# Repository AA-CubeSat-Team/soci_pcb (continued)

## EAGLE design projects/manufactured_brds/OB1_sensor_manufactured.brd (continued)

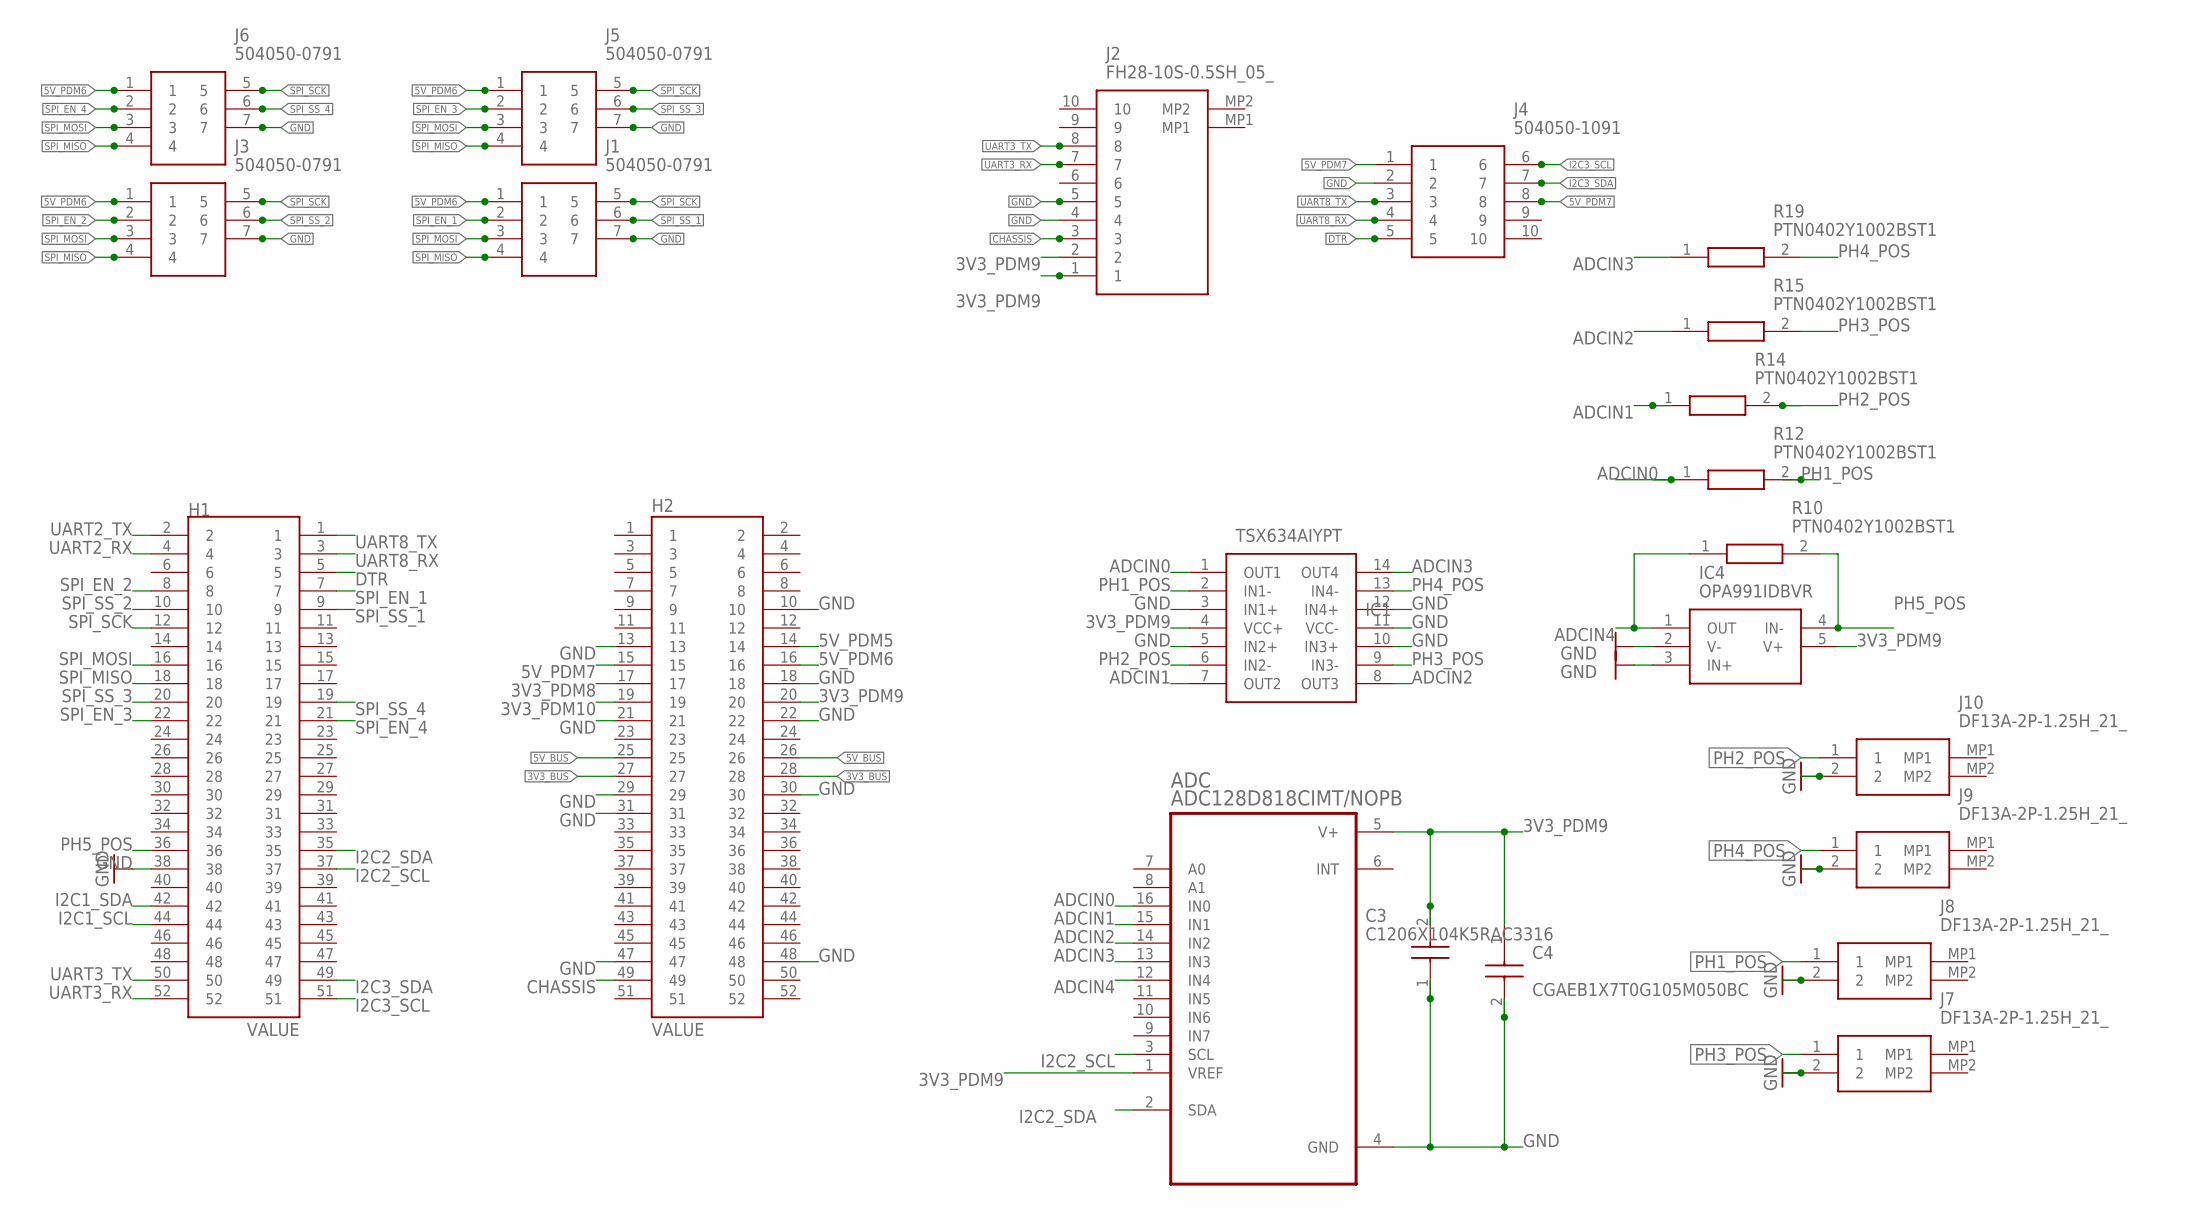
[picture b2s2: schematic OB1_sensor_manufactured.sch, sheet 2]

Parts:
ADC: ADC128D818CIMT/NOPB; SOP65P640X120-16N
C3: C1206X104K5RAC3316; CAPC3316X98N
C4: CGAEB1X7T0G105M050BC; CAPC0611X68N
H1, H2: ESQ-126-39-G-D; SAMTEC_ESQ-126-39-G-D
IC1: TSX634AIYPT; SOP65P640X120-14N
IC4: OPA991IDBVR; SOT95P280X145-5N
J1, J3, J5, J6: 504050-0791
J2: FH28-10S-0.5SH_05_; FH2810S05SH05
J4: 504050-1091
J7, J8, J9, J10: DF13A-2P-1.25H_21_; DF13A2P125H21
R10, R12, R14, R15, R19: PTN0402Y1002BST1; RESC1106X84N

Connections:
3V3_BUS: H2.27, H2.28
3V3_PDM8: H2.17
3V3_PDM9: ADC.1 (VREF), ADC.5 (V+), C3.2, C4.1, H2.20, IC1.4 (VCC+), IC4.5 (V+), J2.1, J2.2; also elsewhere on the board
3V3_PDM10: H2.19
5V_BUS: H2.25, H2.26; also elsewhere on the board
5V_PDM5: H2.14
5V_PDM6: H2.16, J1.1, J3.1, J5.1, J6.1
5V_PDM7: H2.15, J4.1, J4.8
ADCIN0: ADC.16 (IN0), IC1.1 (OUT1), R12.1
ADCIN1: ADC.15 (IN1), IC1.7 (OUT2), R14.1
ADCIN2: ADC.14 (IN2), IC1.8 (OUT3), R15.1
ADCIN3: ADC.13 (IN3), IC1.14 (OUT4), R19.1
ADCIN4: ADC.12 (IN4), IC4.1 (OUT), R10.1
CHASSIS: H2.49, J2.3
DTR: H1.5, J4.5
GND: ADC.4 (GND), C3.1, C4.2, H1.38, H2.10, H2.13, H2.18, H2.21, H2.22, H2.29, H2.30, H2.31, H2.47, H2.48, IC1.3 (IN1+), IC1.5 (IN2+), IC1.10 (IN3+), IC1.11 (VCC-), IC1.12 (IN4+), IC4.2 (V-), IC4.3 (IN+), J1.7, J2.4, J2.5, J3.7, J4.2, J5.7, J6.7, J7.2, J8.2, J9.2, J10.2; also elsewhere on the board
I2C1_SCL: H1.44; also elsewhere on the board
I2C1_SDA: H1.42; also elsewhere on the board
I2C2_SCL: ADC.3 (SCL), H1.37; also elsewhere on the board
I2C2_SDA: ADC.2 (SDA), H1.35; also elsewhere on the board
I2C3_SCL: H1.51, J4.6; also elsewhere on the board
I2C3_SDA: H1.49, J4.7; also elsewhere on the board
PH1_POS: IC1.2 (IN1-), J8.1, R12.2
PH2_POS: IC1.6 (IN2-), J10.1, R14.2
PH3_POS: IC1.9 (IN3-), J7.1, R15.2
PH4_POS: IC1.13 (IN4-), J9.1, R19.2
PH5_POS: H1.36, IC4.4 (IN-), R10.2
SPI_EN_1: H1.7, J1.2
SPI_EN_2: H1.8, J3.2
SPI_EN_3: H1.22, J5.2
SPI_EN_4: H1.21, J6.2
SPI_MISO: H1.18, J1.4, J3.4, J5.4, J6.4
SPI_MOSI: H1.16, J1.3, J3.3, J5.3, J6.3
SPI_SCK: H1.12, J1.5, J3.5, J5.5, J6.5
SPI_SS_1: H1.9, J1.6
SPI_SS_2: H1.10, J3.6
SPI_SS_3: H1.20, J5.6
SPI_SS_4: H1.19, J6.6
UART2_RX: H1.4
UART2_TX: H1.2
UART3_RX: H1.52, J2.7
UART3_TX: H1.50, J2.8
UART8_RX: H1.3, J4.4
UART8_TX: H1.1, J4.3

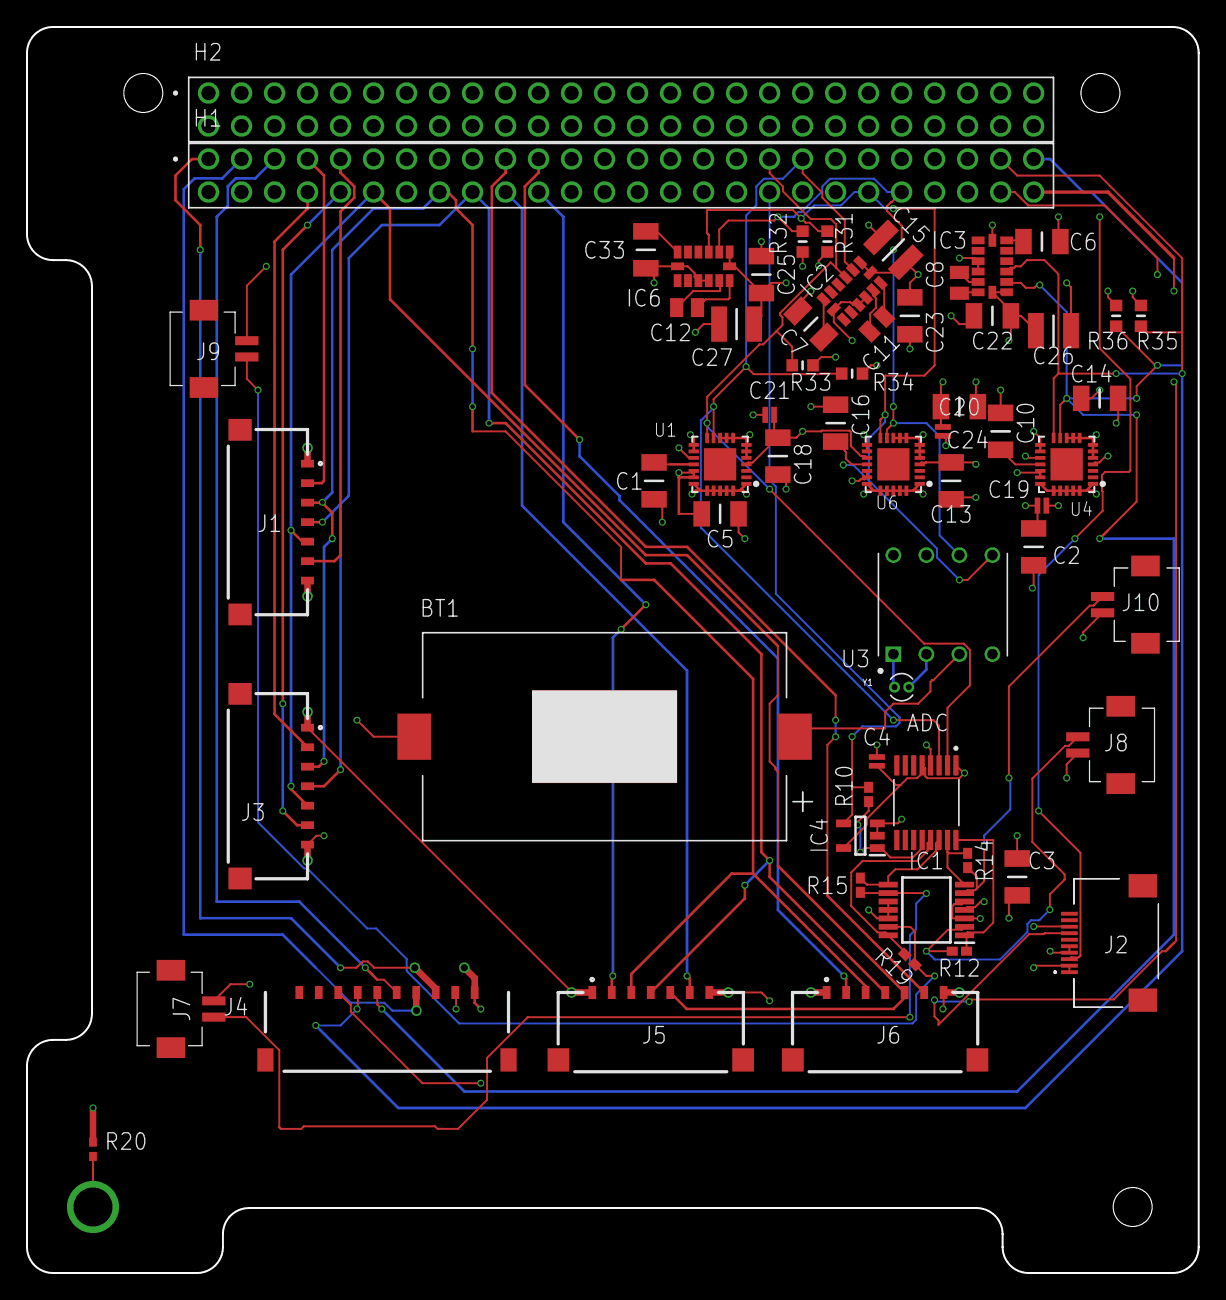
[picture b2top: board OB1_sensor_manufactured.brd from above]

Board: 4 copper layers, 90.2 x 95.9 mm, 62 parts (0 on the bottom side), 54 nets.

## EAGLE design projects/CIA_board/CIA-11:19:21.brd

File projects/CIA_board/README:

Folder containing EAGLE files for the CIA board

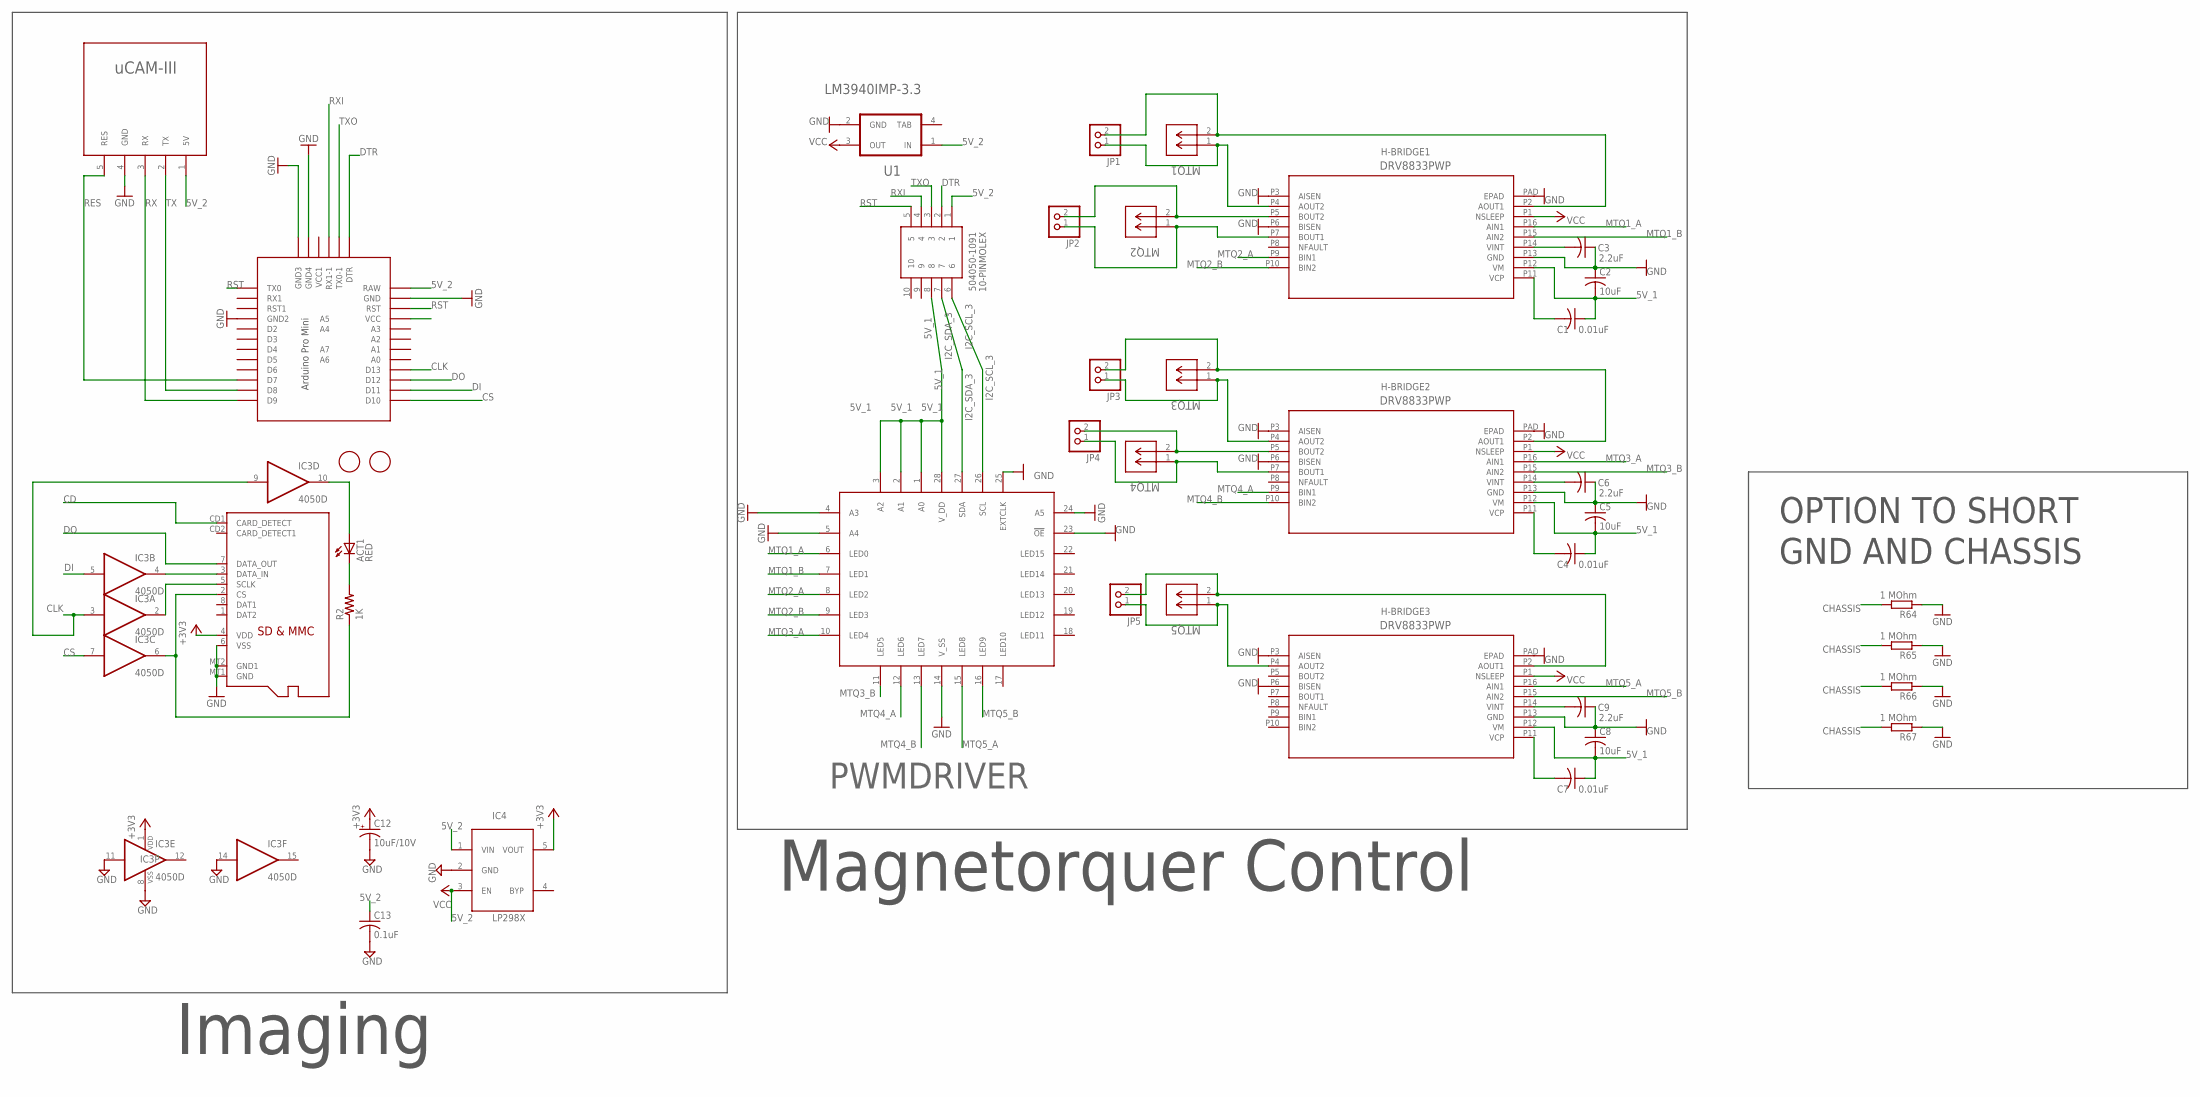
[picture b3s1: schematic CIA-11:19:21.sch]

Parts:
10-PINMOLEX: 504050-1091
ACT1: RED; CHIP-LED0805
C1, C4, C7: 0.01uF; C0603K
C2, C5, C8: 10uF; C1210K
C3, C6, C9: 2.2uF; C0603K
C12: 10uF/10V; A/3216-18R
C13: 0.1uF; C0805K
H-BRIDGE1, H-BRIDGE2, H-BRIDGE3: DRV8833PWP; HTSSOP16
IC3: 4050D; SO16
IC4: LP298XS; SOT23-5L
JP1, JP2, JP3, JP4, JP5: PINHD-1X2; 1X02; MPN 22-11-2022
MTQ1, MTQ2, MTQ3, MTQ4, MTQ5: DF13C-2P-1.25V(51); CON2_1X2_U_DF13
PWMDRIVER: PCA9685PW; TSSOP28
R2: 1K; R0805
R64, R65, R66, R67: 1 MOhm; R0805
U1: TI_NATIONAL_SEMICONDUCTOR_LM3940IMP-3.3TI_NATIONA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; TI_NATIONAL_SEMICONDUCTOR_LM3940IMP-3.3_1
U$2: UCAM-III
U$6, U$7: FIDUCIAL; FIDUCIAL_1MM
U$8: PRO-MINI-2
X2: MICROSD

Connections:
5V_1: 10-PINMOLEX.8, C1.1, C2.2, C4.1, C5.2, C7.1, C8.2, H-BRIDGE1.P12 (VM), H-BRIDGE2.P12 (VM), H-BRIDGE3.P12 (VM), PWMDRIVER.1 (A0), PWMDRIVER.2 (A1), PWMDRIVER.3 (A2), PWMDRIVER.28 (V_DD)
5V_2: 10-PINMOLEX.1, C13.1, IC4.1 (VIN), IC4.3 (EN), U1.1 (IN), U$2.1 (5V), U$8.RAW
+3V3: C12.+, IC3.1 (VDD), IC4.5 (VOUT), X2.4 (VDD)
CD: X2.CD1 (CARD_DETECT)
CHASSIS: R64.2, R65.2, R66.2, R67.2
CLK: IC3.3 (I), IC3.9 (I), U$8.D13
CS: IC3.7 (I), U$8.D10
DI: IC3.5 (I), U$8.D11
DO: U$8.D12, X2.7 (DATA_OUT)
DTR: 10-PINMOLEX.2, U$8.DTR
GND: C2.1, C3.1, C5.1, C6.1, C8.1, C9.1, C12.-, C13.2, H-BRIDGE1.P3 (AISEN), H-BRIDGE1.P6 (BISEN), H-BRIDGE1.P13 (GND), H-BRIDGE1.PAD (EPAD), H-BRIDGE2.P3 (AISEN), H-BRIDGE2.P6 (BISEN), H-BRIDGE2.P13 (GND), H-BRIDGE2.PAD (EPAD), H-BRIDGE3.P3 (AISEN), H-BRIDGE3.P6 (BISEN), H-BRIDGE3.P13 (GND), H-BRIDGE3.PAD (EPAD), IC3.8 (VSS), IC3.11 (I), IC3.14 (I), IC4.2 (GND), PWMDRIVER.4 (A3), PWMDRIVER.5 (A4), PWMDRIVER.14 (V_SS), PWMDRIVER.23 (!OE), PWMDRIVER.24 (A5), PWMDRIVER.25 (EXTCLK), R64.1, R65.1, R66.1, R67.1, U1.2 (GND), U$8.GND, U$8.GND1 (GND2), U$8.GND2 (GND3), U$8.GND3 (GND4), X2.6 (VSS), X2.MT1 (GND), X2.MT2 (GND1)
I2C_SCL_3: 10-PINMOLEX.6, PWMDRIVER.26 (SCL)
I2C_SDA_3: 10-PINMOLEX.7, PWMDRIVER.27 (SDA)
MTQ1_A: H-BRIDGE1.P16 (AIN1), PWMDRIVER.6 (LED0)
MTQ1_B: H-BRIDGE1.P15 (AIN2), PWMDRIVER.7 (LED1)
MTQ2_A: H-BRIDGE1.P9 (BIN1), PWMDRIVER.8 (LED2)
MTQ2_B: H-BRIDGE1.P10 (BIN2), PWMDRIVER.9 (LED3)
MTQ3_A: H-BRIDGE2.P16 (AIN1), PWMDRIVER.10 (LED4)
MTQ3_B: H-BRIDGE2.P15 (AIN2), PWMDRIVER.11 (LED5)
MTQ4_A: H-BRIDGE2.P9 (BIN1), PWMDRIVER.12 (LED6)
MTQ4_B: H-BRIDGE2.P10 (BIN2), PWMDRIVER.13 (LED7)
MTQ5_A: H-BRIDGE3.P16 (AIN1), PWMDRIVER.15 (LED8)
MTQ5_B: H-BRIDGE3.P15 (AIN2), PWMDRIVER.16 (LED9)
unnamed: H-BRIDGE2.P2 (AOUT1), JP3.2, MTQ3.2
unnamed: C3.2, H-BRIDGE1.P14 (VINT)
unnamed: H-BRIDGE1.P4 (AOUT2), JP1.1, MTQ1.1
unnamed: H-BRIDGE1.P2 (AOUT1), JP1.2, MTQ1.2
unnamed: H-BRIDGE1.P7 (BOUT1), JP2.1, MTQ2.1
unnamed: H-BRIDGE1.P5 (BOUT2), JP2.2, MTQ2.2
unnamed: C1.2, H-BRIDGE1.P11 (VCP)
unnamed: H-BRIDGE2.P7 (BOUT1), JP4.1, MTQ4.1
unnamed: H-BRIDGE2.P5 (BOUT2), JP4.2, MTQ4.2
unnamed: C6.2, H-BRIDGE2.P14 (VINT)
unnamed: C4.2, H-BRIDGE2.P11 (VCP)
unnamed: H-BRIDGE2.P4 (AOUT2), JP3.1, MTQ3.1
unnamed: H-BRIDGE3.P2 (AOUT1), JP5.2, MTQ5.2
unnamed: C9.2, H-BRIDGE3.P14 (VINT)
unnamed: C7.2, H-BRIDGE3.P11 (VCP)
unnamed: H-BRIDGE3.P4 (AOUT2), JP5.1, MTQ5.1
unnamed: ACT1.A, IC3.10 (O)
unnamed: IC3.2 (O), X2.5 (SCLK)
unnamed: IC3.6 (O), R2.1, X2.2 (CS)
unnamed: ACT1.C, R2.2
unnamed: IC3.4 (O), X2.3 (DATA_IN)
RES: U$2.5 (RES), U$8.D7
RST: 10-PINMOLEX.5, U$8.RST
RX: U$2.3 (RX), U$8.D9
RXI: 10-PINMOLEX.4, U$8.RX1-1
TAB: U1.4 (TAB)
TX: U$2.2 (TX), U$8.D8
TXO: 10-PINMOLEX.3, U$8.TX0-1
VCC: H-BRIDGE1.P1 (NSLEEP), H-BRIDGE2.P1 (NSLEEP), H-BRIDGE3.P1 (NSLEEP), U1.3 (OUT)

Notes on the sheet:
Imaging
Magnetorquer Control
OPTION TO SHORT
GND AND CHASSIS

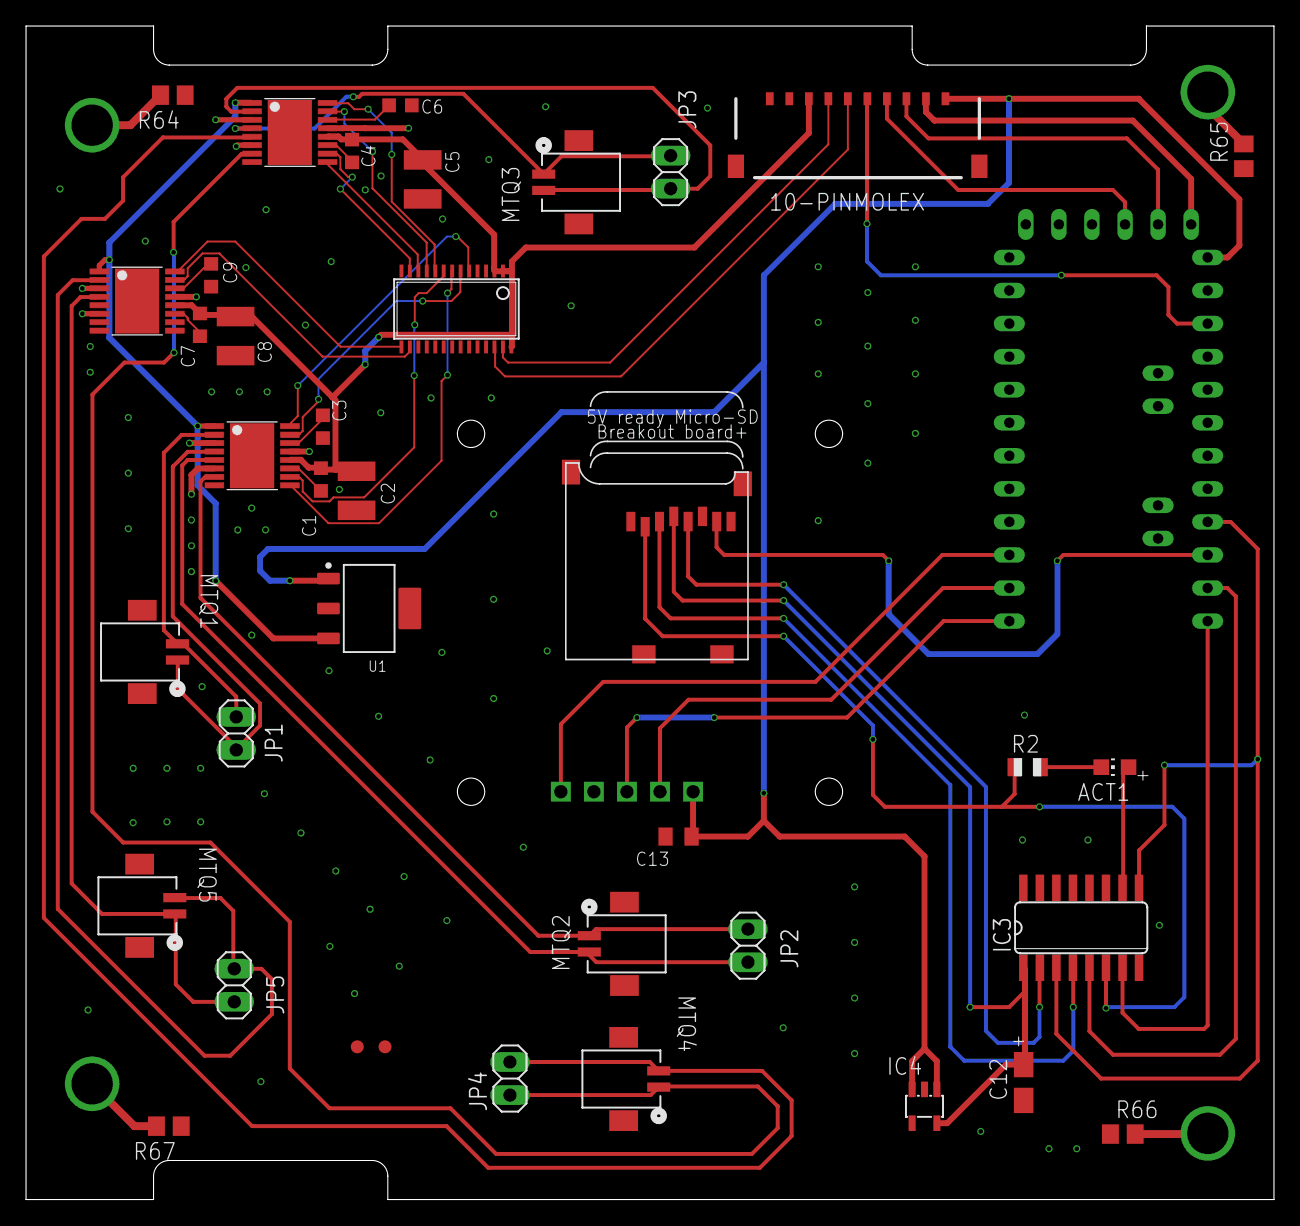
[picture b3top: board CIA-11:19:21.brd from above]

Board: 4 copper layers, 95.9 x 90.2 mm, 40 parts (0 on the bottom side), 50 nets.

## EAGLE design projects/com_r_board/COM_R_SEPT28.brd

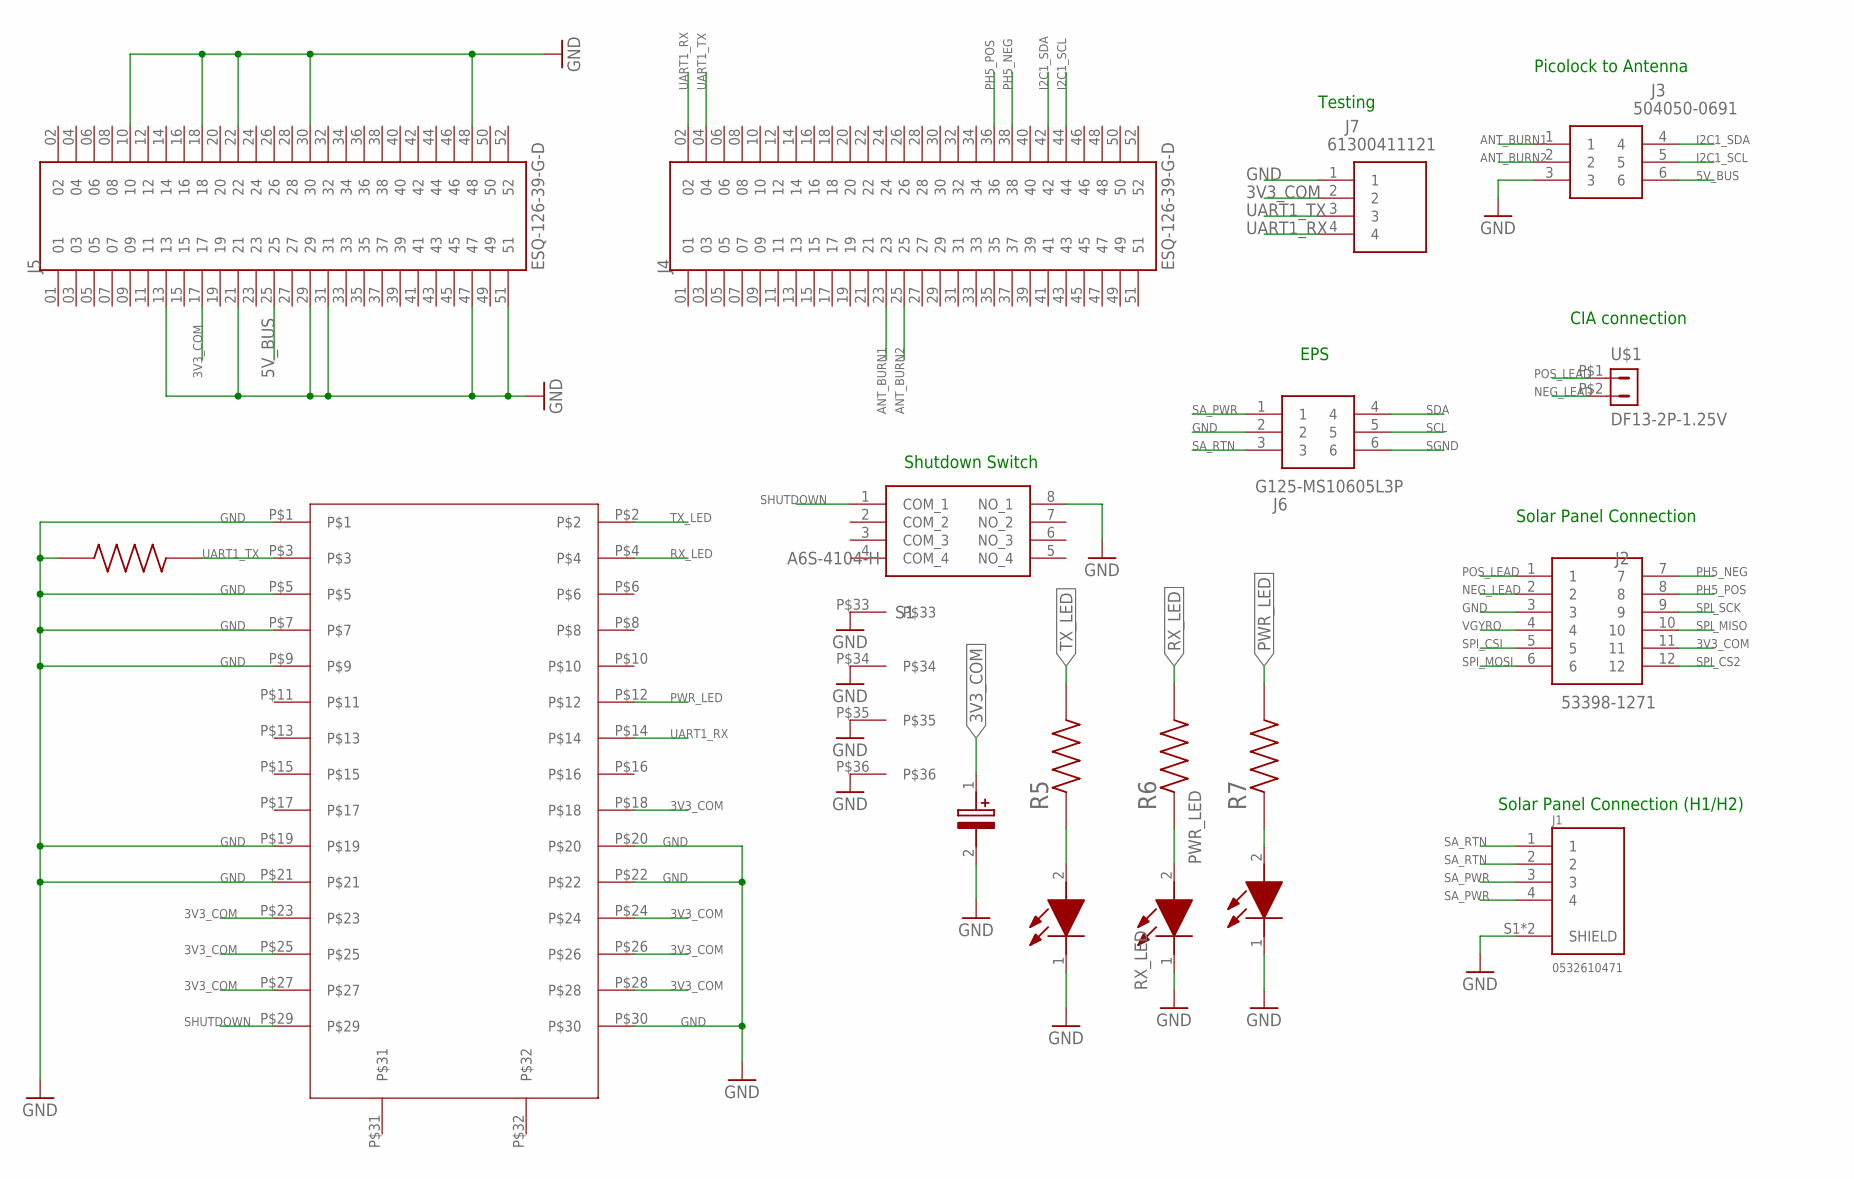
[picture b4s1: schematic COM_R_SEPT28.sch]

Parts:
C2: 293D106X0010A2TE3; CAPPM3216X180N
J1: 0532610471; MOLEX_0532610471
J2: 53398-1271
J3: 504050-0691; 504050-0691_2
J4, J5: ESQ-126-39-G-D; SAMTEC_ESQ-126-39-G-D
J6: G125-MS10605L3P
J7: 61300411121; HDRV4W95P0X254_1X4_1016X254X85
PWR_LED: HSMQ-C170-T0000; LEDC2012X90N
R3: TNPW080510K0BETY; RESC2012X55N
R5, R6, R7: Y40621K00000Q0R; RESC2012X64N
RX_LED: HSMQ-C170-T0000; LEDC2012X90N
S1: A6S-4104-H; A6S4104H
TX_LED: HSMQ-C170-T0000; LEDC2012X90N
U$1: DF13-2P-1.25V; DF13C-2P-1.25V
U$3: KYOCERA_5046_30PIN

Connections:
3V3_COM: C2.1 (+), J2.11, J5.17, J7.2, U$3.P$18, U$3.P$23, U$3.P$24, U$3.P$25, U$3.P$26, U$3.P$27, U$3.P$28
5V_BUS: J3.6, J5.25
ANT_BURN1: J3.1, J4.23
ANT_BURN2: J3.2, J4.25
GND: C2.2 (-), J1.S1 (SHIELD), J1.S2 (SHIELD), J2.3, J3.3, J5.10, J5.13, J5.18, J5.21, J5.22, J5.29, J5.30, J5.31, J5.47, J5.48, J5.51, J6.2, J7.1, PWR_LED.1 (K), R3.1, RX_LED.1 (K), S1.8 (NO_1), TX_LED.1 (K), U$3.P$1, U$3.P$5, U$3.P$7, U$3.P$9, U$3.P$19, U$3.P$20, U$3.P$21, U$3.P$22, U$3.P$30, U$3.P$33, U$3.P$34, U$3.P$35, U$3.P$36
I2C1_SCL: J3.5, J4.44
I2C1_SDA: J3.4, J4.42
unnamed: R5.1, TX_LED.2 (A)
unnamed: PWR_LED.2 (A), R7.1
unnamed: R6.1, RX_LED.2 (A)
NEG_LEAD: J2.2, U$1.P$2 (2)
PH5_NEG: J2.7, J4.38
PH5_POS: J2.8, J4.36
POS_LEAD: J2.1, U$1.P$1 (1)
PWR_LED: R7.2, U$3.P$12
RX_LED: R6.2, U$3.P$4
SA_PWR: J1.3, J1.4, J6.1
SA_RTN: J1.1, J1.2, J6.3
SCL: J6.5
SDA: J6.4
SGND: J6.6
SHUTDOWN: S1.1 (COM_1), U$3.P$29
SPI_CS2: J2.12
SPI_CSI: J2.5
SPI_MISO: J2.10
SPI_MOSI: J2.6
SPI_SCK: J2.9
TX_LED: R5.2, U$3.P$2
UART1_RX: J4.02, J7.4, U$3.P$14
UART1_TX: J4.04, J7.3, R3.2, U$3.P$3
VGYRO: J2.4

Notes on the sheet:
Solar Panel Connection
Picolock to Antenna
Solar Panel Connection (H1/H2)
Shutdown Switch
CIA connection
EPS
Testing

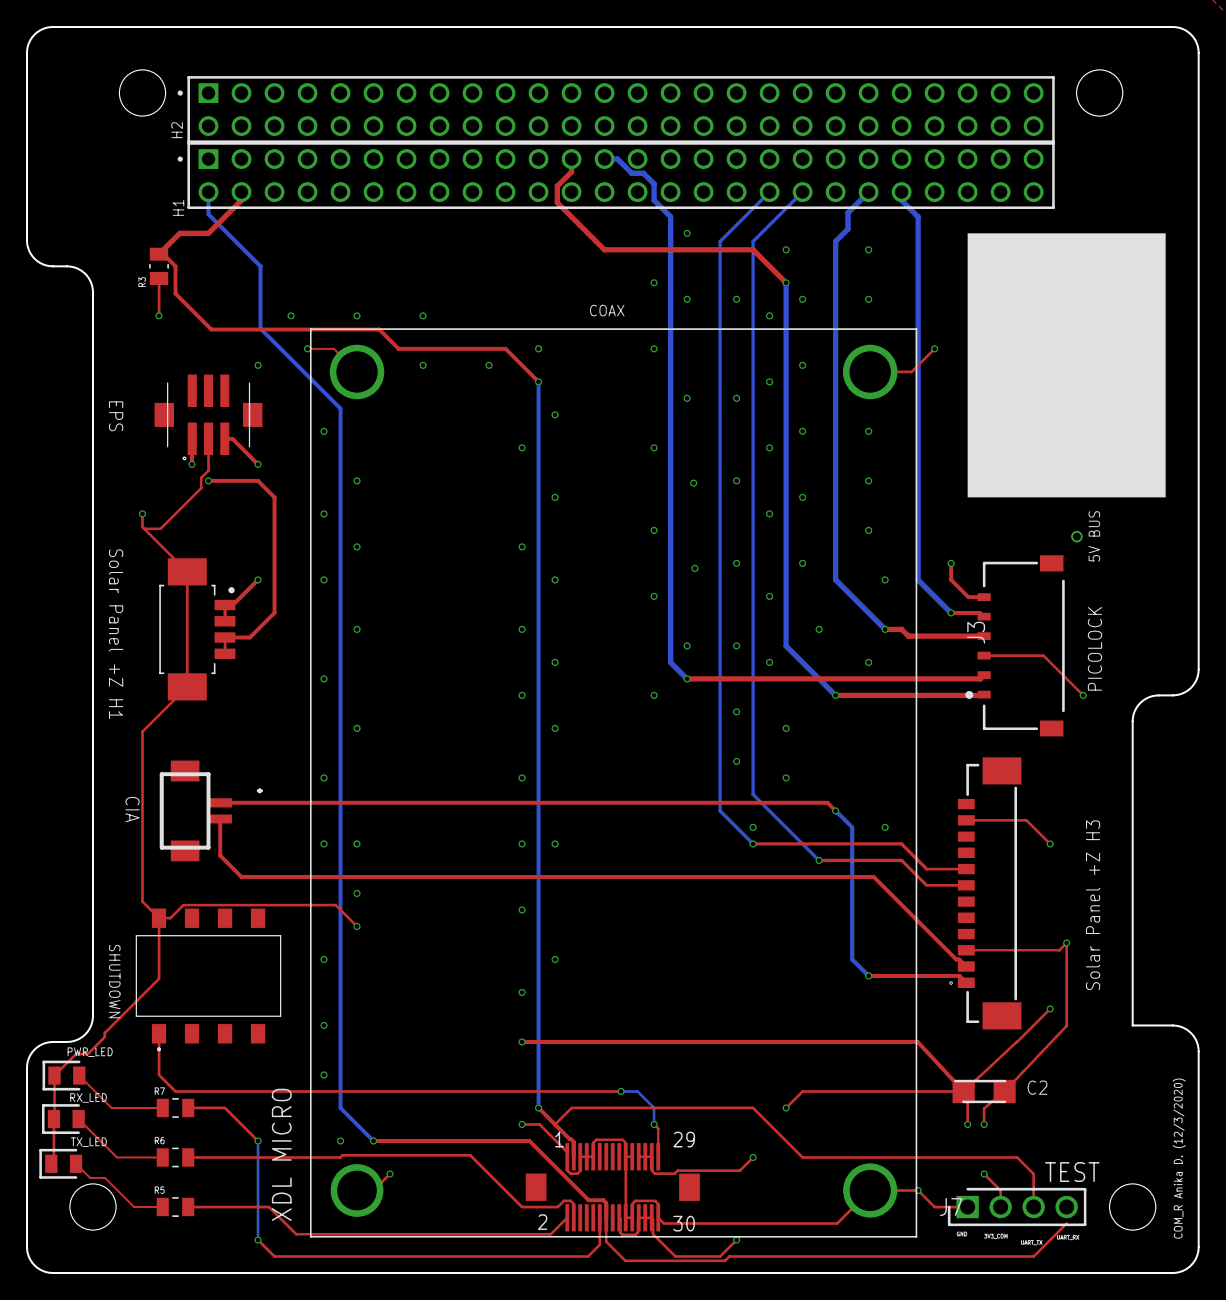
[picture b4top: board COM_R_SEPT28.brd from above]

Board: 4 copper layers, 90.2 x 95.9 mm, 18 parts (0 on the bottom side), 22 nets.

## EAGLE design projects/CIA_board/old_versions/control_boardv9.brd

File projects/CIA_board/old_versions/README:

# Backup Files
Folder containing backup EAGLE files for the CIA board

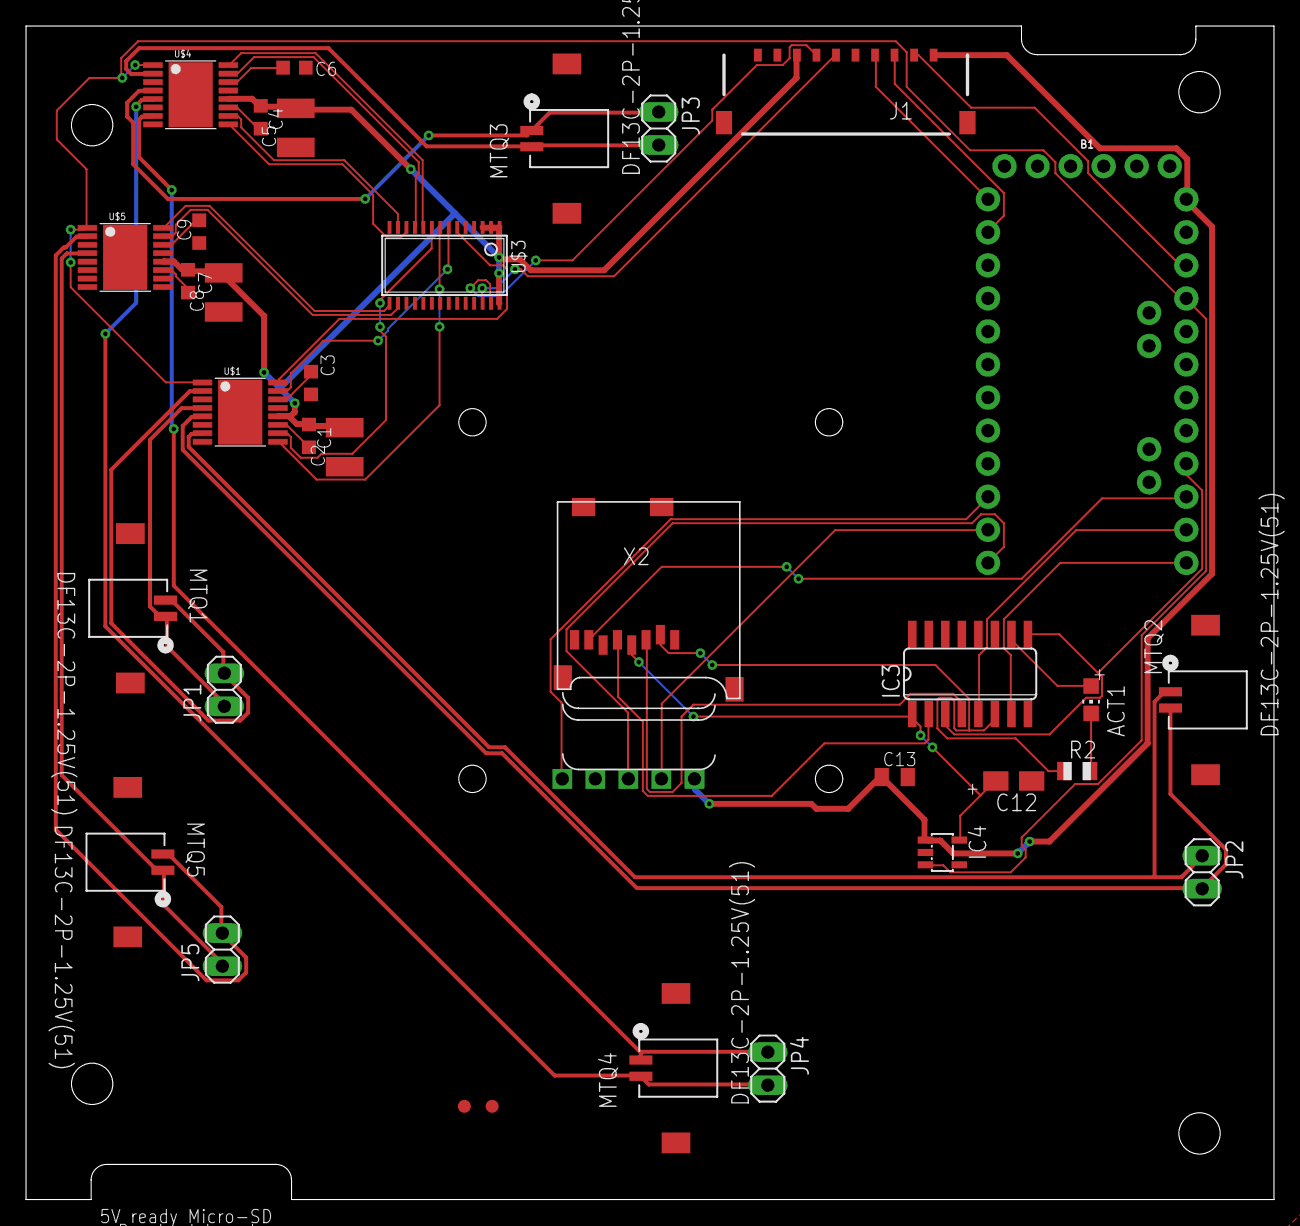
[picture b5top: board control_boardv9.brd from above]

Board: 2 copper layers, 95.9 x 90.2 mm, 35 parts (0 on the bottom side), 48 nets.

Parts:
ACT1: RED; CHIP-LED0805
B1: ARDUINO_PRO_MINI
C1, C4, C7: 0.01uF; C0603K
C2, C5, C8: 10uF; C1210K
C3, C6, C9: 2.2uF; C0603K
C12: 10uF/10V; A/3216-18R
C13: 0.1uF; C0805K
IC3: 4050D; SO16
IC4: LP298XS; SOT23-5L
J1: 504050-1091
JP1, JP2, JP3, JP4, JP5: 1X02
MTQ1, MTQ2, MTQ3, MTQ4, MTQ5: DF13C-2P-1.25V(51); CON2_1X2_U_DF13
R2: 1K; R0805
U$1, U$4, U$5: DRV8833PWP; HTSSOP16
U$2: UCAM-III
U$3: PCA9685PW; TSSOP28
U$6, U$7: FIDUCIAL; FIDUCIAL_1MM
X2: MICROSD

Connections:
5V_1: C1.1, C2.2, C4.1, C5.2, C7.1, C8.2, J1.8, U$1.P12, U$3.1, U$3.2, U$3.3, U$3.28, U$4.P12, U$5.P12
5V_2: B1.24, C13.1, IC4.1, J1.1, U$2.1
+3V3: C12.+, IC3.1, IC4.5, X2.4
CLK: B1.16, IC3.3, IC3.9
CS: B1.13, IC3.7
DI: B1.14, IC3.5
DO: B1.15, X2.7
GND: B1.4, B1.23, C2.1, C3.1, C5.1, C6.1, C8.1, C9.1, C12.-, C13.2, IC3.8, IC3.11, IC3.14, IC4.2, J1.9, U$1.P3, U$1.P6, U$1.P13, U$2.4, U$3.4, U$3.5, U$3.14, U$3.23, U$3.24, U$3.25, U$4.P3, U$4.P6, U$4.P13, U$5.P3, U$5.P6, U$5.P13, X2.6, X2.MT1, X2.MT2
MTQ1_A: U$1.P16, U$3.6
MTQ1_B: U$1.P15, U$3.7
MTQ2_A: U$1.P9, U$3.8
MTQ2_B: U$1.P10, U$3.9
MTQ3_A: U$3.10, U$4.P16
MTQ3_B: U$3.11, U$4.P15
MTQ4_A: U$3.12, U$4.P9
MTQ4_B: U$3.13, U$4.P10
MTQ5_A: U$3.15, U$5.P16
MTQ5_B: U$3.16, U$5.P15
unnamed: JP3.2, MTQ3.2, U$4.P2
unnamed: C3.2, U$1.P14
unnamed: JP1.1, MTQ1.1, U$1.P4
unnamed: JP1.2, MTQ1.2, U$1.P2
unnamed: JP2.1, MTQ2.1, U$1.P7
unnamed: JP2.2, MTQ2.2, U$1.P5
unnamed: C1.2, U$1.P11
unnamed: JP4.1, MTQ4.1, U$4.P7
unnamed: JP4.2, MTQ4.2, U$4.P5
unnamed: C6.2, U$4.P14
unnamed: C4.2, U$4.P11
unnamed: JP3.1, MTQ3.1, U$4.P4
unnamed: JP5.2, MTQ5.2, U$5.P2
unnamed: C9.2, U$5.P14
unnamed: C7.2, U$5.P11
unnamed: JP5.1, MTQ5.1, U$5.P4
unnamed: ACT1.A, IC3.10
unnamed: IC3.2, X2.5
unnamed: IC3.6, R2.1, X2.2
unnamed: ACT1.C, R2.2
unnamed: IC3.4, X2.3
unnamed: B1.10, U$2.5
RST: B1.22, J1.2
RX: B1.12, U$2.3
RXI: B1.2, J1.3
SCL: J1.6, U$3.26
SDA: J1.7, U$3.27
TX: B1.11, U$2.2
TXO: B1.1, J1.4
VCC: B1.21, IC4.3, U$1.P1, U$4.P1, U$5.P1

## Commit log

2020-09-15 Initial commit. Setup 4 initial project folders and created directory for libraries and design rules.
2020-09-15 Added some readme files
2020-09-15 Updates to sensor board. Routed sensors
2020-09-15 Updated sensor board. First revision of completely routed board
2020-09-15 Added oshpark 2 layer design rule, updated gyroscope library, added new gyroscope footprint to sensor board
2020-09-25 Converted sensor board to 4 layers. Re-routed magnetometers/gyros and ripped up most other traces
2020-09-25 Completed first revision of 4 layer sensor board
2020-10-02 Added first draft of COM_R test board, schematic only.
2020-11-11 RT1020 libraries added, OBC routed for RT1020
2020-11-11 sensor board updated
2020-12-09 COM_R_BOARD revision 1. 12/8/2020
2020-12-09 COM_R revision 1. 12/8/2020
2021-01-28 Fixed mounting hole dimensions
2021-02-23 Fixed PC104 mounting holes and updated pc104 pinouts to be updated
2021-06-24 Thomas edits to COM_R flipped PC104 header
2021-09-18 new OBC files
2021-09-24 Update sensor.brd
    Updated with fix to I2C lines
2021-09-24 Update sensor.sch
    Updated with fix to I2C lines
2021-10-23 Fixed mounting holes
    Changed by Andy Xiong!
2021-10-27 Add files via upload
    updated OBC with revisions and added a 20 pin jtag connector
2021-11-12 Add files via upload
    updated CIA board eagle files:
    - Re routed imaging side of CIA board to troubleshoot/fix issues
    - Adjusted design language (wider traces, better spacing, etc)
2021-11-12 Create Read me
2021-11-12 Update and rename Read me to README
2021-11-12 Rename README to README.md
2021-11-12 Rename obc.brd to obc_old.brd
2021-11-12 Rename obc.sch to obc_old.sch
2021-12-10 Add files via upload
    Eagle files for manufactured boards - MacroFab: November, 2021
